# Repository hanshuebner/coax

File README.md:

# coax

Tools for connecting to real [IBM 3270](https://en.wikipedia.org/wiki/IBM_3270) type terminals.

## Documentation

* [protocol](protocol/protocol.md) - Protocol documentation

## Hardware

* [interface1](interface1) - Legacy interface using obsolete National Semiconductor DP8340 and DP8341
* [interface2](interface2) - Modern interface using a Lattice iCE40 FPGA and STM32 microcontroller
* [interface3](interface3) - WiFi interface based on Raspberry Pi Pico W

## Software

* [pycoax](pycoax) - Python interface library

## See Also

* [oec](https://github.com/hanshuebner/oec) - IBM 3270 terminal controller (a replacement for the IBM 3174)

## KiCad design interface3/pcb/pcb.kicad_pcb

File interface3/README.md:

# Interface3 - Raspberry Pi Pico W based 3270 Terminal Adapter

Interface3 is an alternative hardware solution to connect a 3270 coax
terminal to host systems through the oec terminal controller software
written by Andrew Kay.  It consists of a Raspberry Pi Pico-based
hardware interface and MicroPython software that implements the coax
protocol used by 3270 terminals in CUT mode.

## Overview

Interface3 enables communication with IBM 3270 terminals by:

1. **Hardware Interface**: A custom PCB with a Raspberry Pi Pico and
   up to four serial coax interfaces that implement the physical layer
   connection to 3270 terminals.
2. **Protocol Implementation**: The Manchester-encoded coax protocol
   is implemented using PIO blocks of the RP2040 microcontroller.
3. **Connection Modes**: Two connection modes are supported:
   - **Serial Mode**: Direct USB serial connection to a host running
     oec/pycoax, compatible with interface2.  Requires Andrew Kay's
     original [oec](https://github.com/lowobservable/oec).
   - **WiFi Mode**: TCP client that connects to an oec server over
     WiFi using a custom binary protocol.  Requires the modified
     [oec-tcp](https://github.com/hanshuebner/oec-tcp).

## How It Works

### Hardware Layer
The interface uses a Raspberry Pi Pico with custom PCB that provides:
- Two Coax interfaces with proper signal conditioning
- Two additional serial interfaces with TTL levels on a pin header
- LED indicators to display the operating state of the interface
- Momentary button that resets the Raspberry Pi Pico
- USB B socket for power supply and serial connection

### Software Layer

The interface3 software implements the line level Manchester-encoded
protocol in a
[PIO](https://www.raspberrypi.com/news/what-is-pio/) block.  This
offloads the handling of the real-time protocol requirements from the
main ARM CPU and allows the rest of the interface software to be
implemented in MicroPython.  Data between MicroPython and the PIO
blocks is exchanged through DMA, allowing the MicroPython part to
operate only on full frames.

## Installation

### Prerequisites

1. **MicroPython with DMA Extensions**: You need a MicroPython release
   1.26.0 or later to get support for the DMA transfer library
   required by the firmware.

2. **Hardware**: The interface3 PCB with Raspberry Pi Pico installed

3. **Development Tools**:
   - `mpremote` for communicating with the Pico
   - `jq` for JSON processing (used by config-wifi.sh, WiFi mode only)

### Common Installation Steps

1. **Flash MicroPython Firmware**:

   A prebuilt MicroPython image for the Raspberry Pi Pico W (RP2040
   version) can be downloaded from
   [my web site](https://vaxbusters.org/micropython-v1.26.0-rpi-pico-w.uf2).
   Connect the Raspberry Pi Pico W to your workstation using its Micro USB
   port while holding the small white "BOOTSEL" button, then copy the
   image to the USB drive that automatically appears (mounted as
   `/Volumes/RPI-RP2/` on Macs).

2. **Install mpremote**

   You can either install mpremote from your system's package repository
   or using pip.  When using pip, using a virtual environment is
   recommended:

   ```bash
   python -m venv .venv
   . .venv/bin/activate
   pip install mpremote
   ```

3. **Upload and install the firmware** using the install script:

   ```bash
   ./install.sh serial   # For serial mode
   ./install.sh wifi     # For WiFi mode
   ```

   The install script will upload all required files and configure
   the device for the selected mode.

### Updating the Firmware

The firmware restarts the Pico into its USB bootloader when any of its
serial ports is opened at 1200 baud, so a new image can be loaded from
the host it is attached to.  `tools/flash-interface <image.uf2>` does
this end to end: it triggers the restart, waits for the bootloader's
USB drive, copies the image onto it and waits for the interface to come
back.  A board whose firmware predates that hook is put into the
bootloader by hand once, by holding BOOTSEL while pressing reset; the
script waits for it.

### Serial Mode Setup

After running `./install.sh serial`, the device is ready to use.
Connect to the interface using oec (see Usage section below).

### WiFi Mode Setup

After running `./install.sh wifi`, configure WiFi credentials:

```bash
./config-wifi.sh
```

This interactive script will:
- Prompt for WiFi network name and password
- Prompt for the hostname of the oec server
- Create a `config.json` file on the device
- Reset the device to apply the configuration

For testing, you can use my oec server running at netzhansa.com.
It is located in Germany, however, so the latency may be quite
high.  If you run oec on a port other than 3174, you can enter it
after the hostname, colon separated (host:port).

The device stores configuration in a `config.json` file:
```json
{
  "wifi": {
    "ssid": "your_network_name",
    "password": "your_network_password"
  },
  "connect_to": "your-oec-server.example.com"
}
```

## Usage

### Serial Mode

Serial mode requires Andrew Kay's original oec repository:
https://github.com/lowobservable/oec

Run oec with the serial port:

```bash
python -m oec /dev/tty.usbmodem* tn3270 your-host.example.com:23
```

Replace `/dev/tty.usbmodem*` with the actual device path (e.g.,
`/dev/tty.usbmodem1124101` on macOS, `/dev/ttyACM0` on Linux, or
`COM3` on Windows).

The interface presents five serial ports: one per coax port, followed
by the capture port.  Name the port you want explicitly rather than
relying on a glob.

#### Accessing the Python REPL

During startup, the firmware provides a 5-second window to access the
MicroPython REPL for debugging or configuration.  To access the REPL:

1. **Connect to the USB serial port** before or immediately after
   resetting the device.  Use a terminal program or mpremote:
   ```bash
   mpremote connect /dev/tty.usbmodem* repl
   ```

2. **Watch for the startup blink pattern** - the STS LED blinks slowly
   (250ms on, 250ms off) during this 5-second window.

3. **Press Ctrl-C** during this window to interrupt startup and enter
   the REPL.

**Important**: You must connect to the serial port *before* the
startup window expires.  Once the firmware enters protocol mode, the
serial port is used exclusively for SLIP-encoded communication and
keyboard interrupt is disabled.

### WiFi Mode

WiFi mode requires a modified version of oec that acts as a TCP server:
https://github.com/hanshuebner/oec-tcp

Start the oec-tcp server:

```bash
python -m oec --server :3174 tn3270 your-host.example.com:23
```

This starts oec listening on port 3174 for incoming connections from
interface3 devices.  When the interface connects to WiFi successfully,
it will automatically connect to the configured server.

See the [TCP Protocol documentation](./TCP_PROTOCOL.md) for details on
the network protocol.

### Capturing Coax Traffic

The interface can record the coax traffic it exchanges with attached
terminals and hand it to Wireshark.  Capture happens in the firmware,
so both directions of every transaction are recorded as they appear on
the wire, with microsecond timestamps.

Records leave the device on a fifth USB serial port named `Coax
Capture`, which the four command ports are unaffected by.  Write a
capture file with:

```bash
tools/coax-capture --write coax.pcapng
```

To capture from the Wireshark GUI, install the capture plugin and the
dissector once:

```bash
tools/install-wireshark.sh
```

Idle polls are left out unless `--idle-polls` is given, since a
terminal is polled continuously.  See the [capture
documentation](./CAPTURE.md) for the record format, the filtering
options and the pcapng layout.

The interface can also record a link between some other controller and
a terminal, either sitting in the middle of it and forwarding between
two ports, or listening on one:

```bash
tools/coax-capture --forward 0,1 --write link.pcapng
tools/coax-capture --tap 0 --write tap.pcapng
```

See [Passive Capture](./PASSIVE-CAPTURE.md) for how to connect the
interface to a link and what to expect.  Forwarding needs a second coax
port that can transmit; boards built from the earlier layout need the
rework described in [PCB Rework](./PCB-REWORK.md).

## LED Indicators

The interface provides several LED indicators:
- **NET**: Network activity (WiFi mode only)
- **STS**: Status indicator
- **ERR**: Error indicator
- **TX1-4/RX1-4**: Individual channel transmit/receive indicators
- **PICO**: Raspberry Pi Pico onboard LED

### Serial Mode LED Patterns

| LED | Pattern | Description |
|-----|---------|-------------|
| STS | Slow blink (250ms on/off) | **Startup window** - Press Ctrl-C to access REPL |
| STS | Fast blink (100ms on, 200ms off) | **Waiting for connection** - Ready for host to connect |
| STS | Once per second (100ms on, 900ms off) | **Connected** - Normal operation |
| ERR | Continuous fast blink (250ms on/off) | **Fatal error** - Unhandled exception occurred |

### WiFi Mode LED Patterns

| LED | Pattern | Description |
|-----|---------|-------------|
| NET | Fast blink (8Hz) | **Connecting to WiFi** - Attempting to join network |
| NET | Brief on, then off | **WiFi connected** - Successfully joined network |
| NET | On during activity | **Network activity** - Processing commands from server |
| STS | Solid on | **Connecting to server** - Attempting TCP connection |
| STS | Blink (1s on, 1s off) | **Reconnecting** - Connection lost, retrying |
| ERR | Solid on | **WiFi failed** - Could not connect to WiFi network |
| ERR | Solid on | **Coax timeout** - Terminal not responding (clears on success) |

## Quick Reference

| Mode | oec Repository | Command |
|------|----------------|---------|
| Serial | [lowobservable/oec](https://github.com/lowobservable/oec) | `python -m oec /dev/ttyUSB0 tn3270 host:port` |
| WiFi | [hanshuebner/oec-tcp](https://github.com/hanshuebner/oec-tcp) | `python -m oec --server :3174 tn3270 host:port` |

## License

Copyright (c) 2025, Hans Hübner

Permission to use, copy, modify, and/or distribute this software for any
purpose with or without fee is hereby granted, provided that the above
copyright notice and this permission notice appear in all copies.

THE SOFTWARE IS PROVIDED "AS IS" AND THE AUTHOR DISCLAIMS ALL WARRANTIES
WITH REGARD TO THIS SOFTWARE INCLUDING ALL IMPLIED WARRANTIES OF
MERCHANTABILITY AND FITNESS. IN NO EVENT SHALL THE AUTHOR BE LIABLE FOR
ANY SPECIAL, DIRECT, INDIRECT, OR CONSEQUENTIAL DAMAGES OR ANY DAMAGES
WHATSOEVER RESULTING FROM LOSS OF USE, DATA OR PROFITS, WHETHER IN AN
ACTION OF CONTRACT, NEGLIGENCE OR OTHER TORTIOUS ACTION, ARISING OUT OF
OR IN CONNECTION WITH THE USE OR PERFORMANCE OF THIS SOFTWARE.

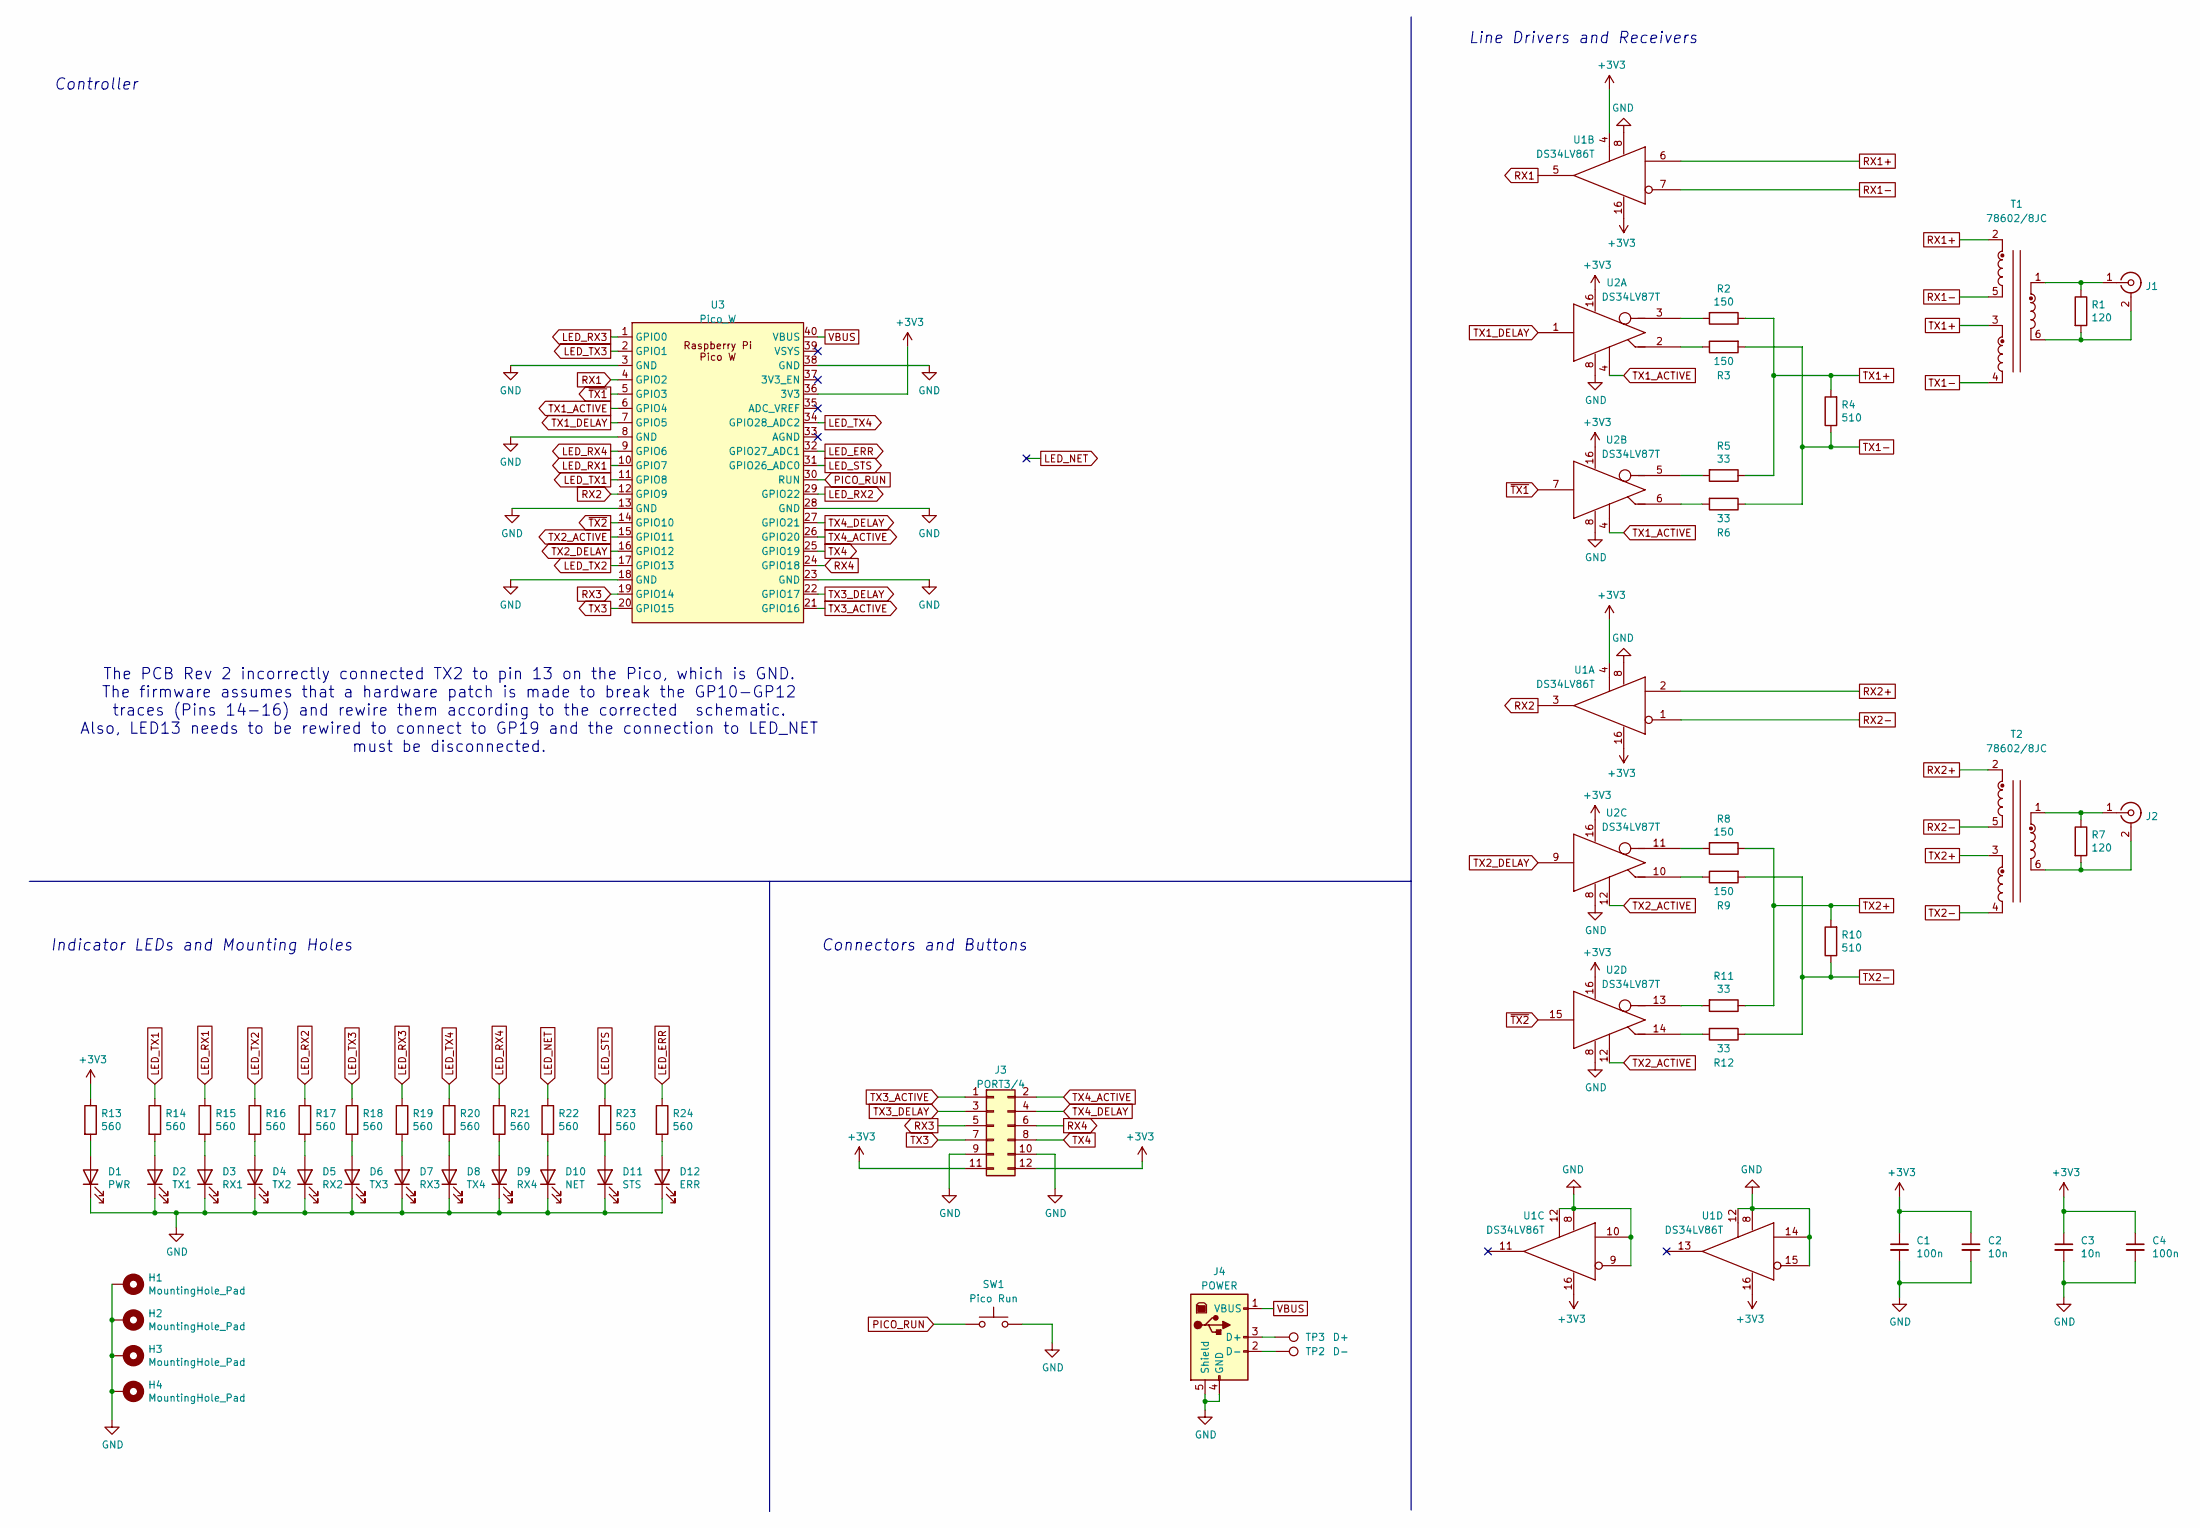
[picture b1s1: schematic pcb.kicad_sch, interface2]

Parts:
C1: 100n; C_0603_1608Metric_Pad1.08x0.95mm_HandSolder; Part EMK107B7104KA-T
C2: 10n; C_0603_1608Metric_Pad1.08x0.95mm_HandSolder; Part HMK107B7103KA-T
C3: 10n; C_0603_1608Metric_Pad1.08x0.95mm_HandSolder; Part EMK107B7104KA-T
C4: 100n; C_0603_1608Metric_Pad1.08x0.95mm_HandSolder; Part HMK107B7103KA-T
D1: PWR; LED_0603_1608Metric; Part 150060VS55040
D2: TX1; LED_0603_1608Metric; Part 150060YS55040
D3: RX1; LED_0603_1608Metric; Part 150060YS55040
D4: TX2; LED_0603_1608Metric; Part 150060YS55040
D5: RX2; LED_0603_1608Metric; Part 150060YS55040
D6: TX3; LED_0603_1608Metric; Part 150060YS55040
D7: RX3; LED_0603_1608Metric; Part 150060YS55040
D8: TX4; LED_0603_1608Metric; Part 150060YS55040
D9: RX4; LED_0603_1608Metric; Part 150060YS55040
D10: NET; LED_0603_1608Metric; Part 150060RS55040
D11: STS; LED_0603_1608Metric; Part 150060RS55040
D12: ERR; LED_0603_1608Metric; Part 150060RS55040
H1, H2, H3, H4: MountingHole_Pad; MountingHole_2.7mm_M2.5_ISO7380_Pad
J1: PORT1; BNC_Amphenol_B6252HB-NPP3G-50_Horizontal; Part 1-1337543-0
J2: PORT2; BNC_Amphenol_B6252HB-NPP3G-50_Horizontal; Part 1-1337543-0
J3: PORT3/4; PinHeader_2x06_P2.54mm_Vertical
J4: POWER; USB_B_OST_USB-B1HSxx_Horizontal
R1, R7: 120; R_0603_1608Metric_Pad0.98x0.95mm_HandSolder; Part RCS0603120RFKEA
R2, R3, R8, R9: 150; R_0603_1608Metric_Pad0.98x0.95mm_HandSolder; Part RCS0603150RFKEA
R4, R10: 510; R_0603_1608Metric_Pad0.98x0.95mm_HandSolder; Part RCS0603510RFKEA
R5, R6, R11, R12: 33; R_0603_1608Metric_Pad0.98x0.95mm_HandSolder; Part RCS060333R0FKEA
R13, R14, R15, R16, R17, R18, R19, R20, R21, R22, R23, R24: 560; R_0603_1608Metric_Pad0.98x0.95mm_HandSolder; Part RCS0603560RFKEA
SW1: Pico Run; SW_Push_1P1T_NO_6x6mm_H9.5mm
T1, T2: 78602/8JC; Murata_786J; Part 78602/8JC
TP2: D-; TestPoint_Pad_D2.0mm
TP3: D+; TestPoint_Pad_D2.0mm
U1: DS34LV86T; SOIC-16_3.9x9.9mm_P1.27mm; Part DS34LV86T
U2: DS34LV87T; SOIC-16_3.9x9.9mm_P1.27mm; Part DS34LV87T
U3: Pico_W; RPi_Pico_W_SMD_TH

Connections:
+3V3: C1.1, C2.1, C3.1, C4.1, J3.11, J3.12, R13.1, U1.4 (ENABLE), U1.16 (VCC), U2.16 (VCC), U3.36 (3V3)
GND: C1.2, C2.2, C3.2, C4.2, D1.1 (K), D2.1 (K), D3.1 (K), D4.1 (K), D5.1 (K), D6.1 (K), D7.1 (K), D8.1 (K), D9.1 (K), D10.1 (K), D11.1 (K), D12.1 (K), H1.1 (1_1), H2.1 (1_1), H3.1 (1_1), H4.1 (1_1), J3.9, J3.10, J4.4 (GND), J4.5 (Shield), SW1.2, U1.8 (GND), U1.9 (E-), U1.10 (E+), U1.12 (ENABLE), U1.14 (E+), U1.15 (E-), U2.8 (GND), U3.3 (GND), U3.8 (GND), U3.13 (GND), U3.18 (GND), U3.23 (GND), U3.28 (GND), U3.38 (GND)
LED_ERR: R24.1, U3.32 (GPIO27_ADC1)
LED_NET: R22.1
LED_RX1: R15.1, U3.10 (GPIO7)
LED_RX2: R17.1, U3.29 (GPIO22)
LED_RX3: R19.1, U3.1 (GPIO0)
LED_RX4: R21.1, U3.9 (GPIO6)
LED_STS: R23.1, U3.31 (GPIO26_ADC0)
LED_TX1: R14.1, U3.11 (GPIO8)
LED_TX2: R16.1, U3.17 (GPIO13)
LED_TX3: R18.1, U3.2 (GPIO1)
LED_TX4: R20.1, U3.34 (GPIO28_ADC2)
unnamed: D1.2 (A), R13.2
unnamed: D2.2 (A), R14.2
unnamed: D3.2 (A), R15.2
unnamed: D4.2 (A), R16.2
unnamed: D5.2 (A), R17.2
unnamed: D6.2 (A), R18.2
unnamed: D7.2 (A), R19.2
unnamed: D8.2 (A), R20.2
unnamed: D9.2 (A), R21.2
unnamed: D10.2 (A), R22.2
unnamed: D11.2 (A), R23.2
unnamed: D12.2 (A), R24.2
unnamed: J1.2 (Ext), R1.2, T1.6
unnamed: J1.1 (In), R1.1, T1.1
unnamed: J2.2 (Ext), R7.2, T2.6
unnamed: J2.1 (In), R7.1, T2.1
unnamed: J4.3 (D+), TP3.1 (1_1)
unnamed: J4.2 (D-), TP2.1 (1_1)
unnamed: R3.1, U2.2 (OUT+)
unnamed: R2.2, U2.3 (OUT-)
unnamed: R6.2, U2.6 (OUT+)
unnamed: R5.2, U2.5 (OUT-)
unnamed: R9.1, U2.10 (OUT+)
unnamed: R8.2, U2.11 (OUT-)
unnamed: R12.2, U2.14 (OUT+)
unnamed: R11.2, U2.13 (OUT-)
PICO_RUN: SW1.1, U3.30 (RUN)
RX1: U1.5 (OUT), U3.4 (GPIO2)
RX1+: T1.2, U1.6 (E+)
RX1-: T1.5, U1.7 (E-)
RX2: U1.3 (OUT), U3.12 (GPIO9)
RX2+: T2.2, U1.2 (E+)
RX2-: T2.5, U1.1 (E-)
RX3: J3.5, U3.19 (GPIO14)
RX4: J3.6, U3.24 (GPIO18)
TX1+: R2.1, R4.2, R5.1, T1.3
TX1-: R3.2, R4.1, R6.1, T1.4
TX1_ACTIVE: U2.4 (ENABLE), U3.6 (GPIO4)
TX1_DELAY: U2.1 (INPUT), U3.7 (GPIO5)
TX2+: R8.1, R10.2, R11.1, T2.3
TX2-: R9.2, R10.1, R12.1, T2.4
TX2_ACTIVE: U2.12 (ENABLE), U3.15 (GPIO11)
TX2_DELAY: U2.9 (INPUT), U3.16 (GPIO12)
TX3: J3.7, U3.20 (GPIO15)
TX3_ACTIVE: J3.1, U3.21 (GPIO16)
TX3_DELAY: J3.3, U3.22 (GPIO17)
TX4: J3.8, U3.25 (GPIO19)
TX4_ACTIVE: J3.2, U3.26 (GPIO20)
TX4_DELAY: J3.4, U3.27 (GPIO21)
VBUS: J4.1 (VBUS), U3.40 (VBUS)
~TX1: U2.7 (INPUT), U3.5 (GPIO3)
~TX2: U2.15 (INPUT), U3.14 (GPIO10)

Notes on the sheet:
Connectors and Buttons
Line Drivers and Receivers
Controller
The PCB Rev 2 incorrectly connected TX2 to pin 13 on the Pico, which is GND. The firmware assumes that a hardware patch is made to break the GP10-GP12 traces (Pins 14-16) and rewire them according to the corrected schematic. Also, LED13 needs to be rewired to connect to GP19 and the connection to L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
Indicator LEDs and Mounting Holes

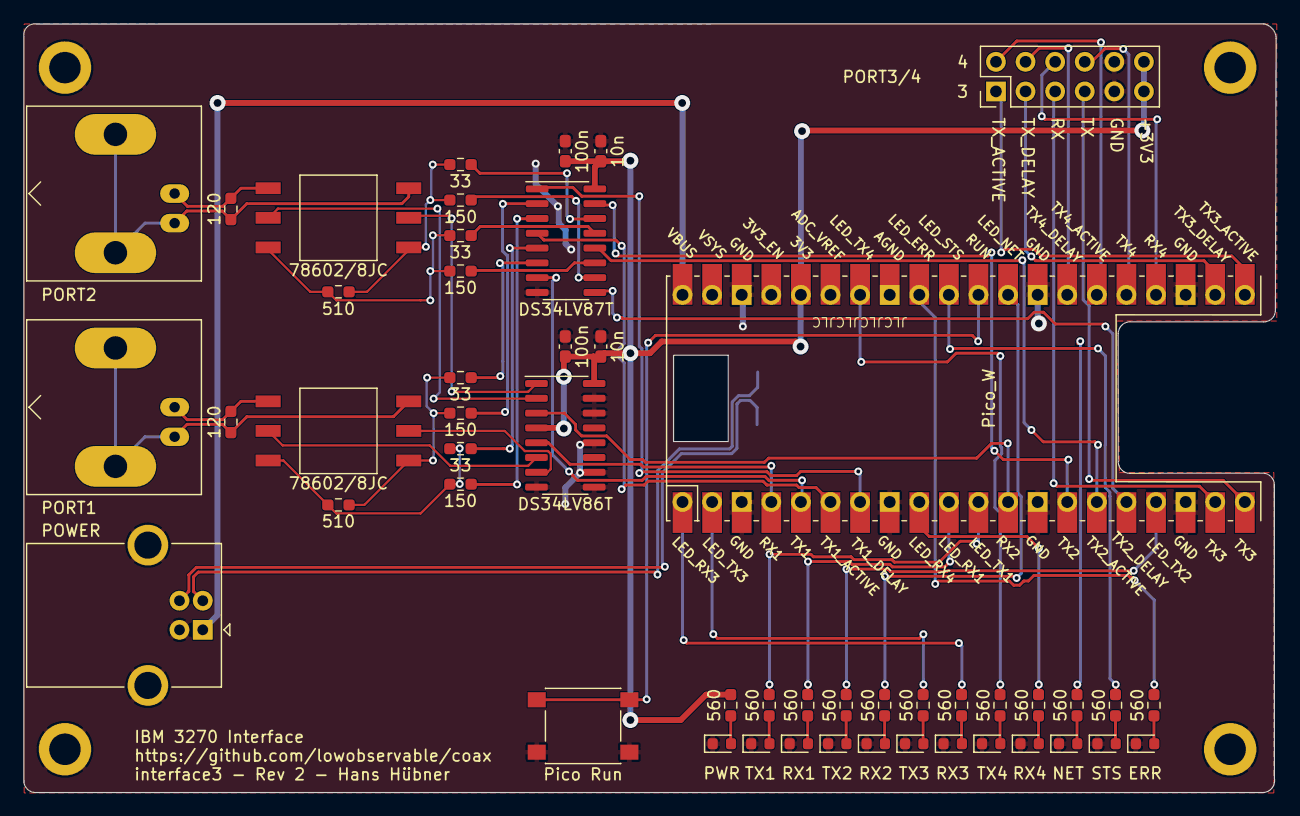
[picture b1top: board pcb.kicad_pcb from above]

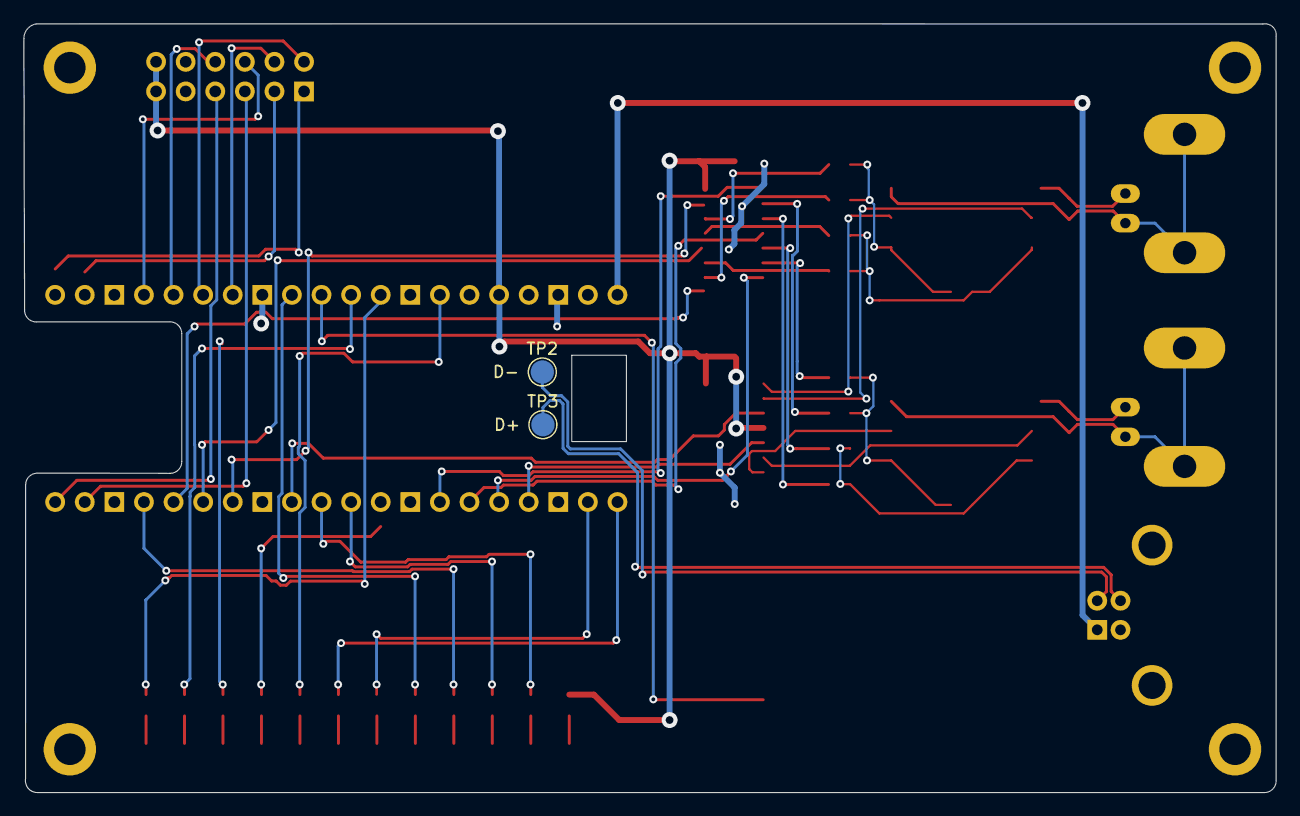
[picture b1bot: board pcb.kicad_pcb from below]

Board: 2 copper layers, 107.5 x 66.0 mm, 56 parts (2 on the bottom side), 64 nets.

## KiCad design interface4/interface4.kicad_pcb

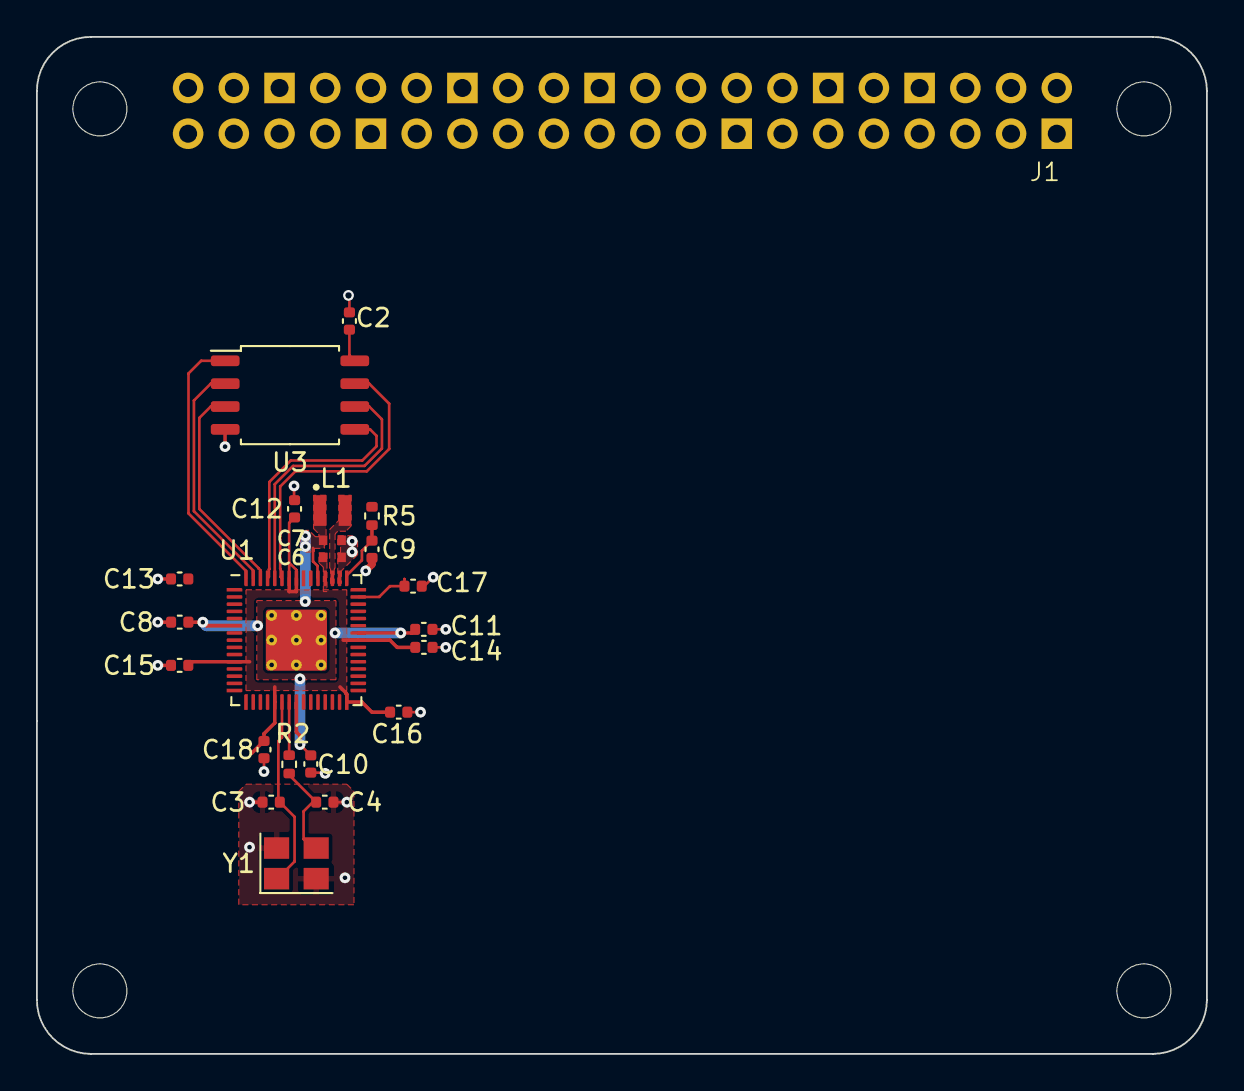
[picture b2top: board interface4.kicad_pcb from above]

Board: 2 copper layers, 65.0 x 56.5 mm, 23 parts (0 on the bottom side), 14 nets.

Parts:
C2, C8, C11, C12, C13, C14, C15, C16, C17, C18: 100n; C_0402_1005Metric
C3, C4: 15p; C_0402_1005Metric
C6, C7: 4.7u; C_0402_1005Metric_small_pads
C9, C10: 4.7u; C_0402_1005Metric
J1: RPi_GPIO; RPI_Hat_B+
L1: 3.3u; L_pol_2016
R2: 1k; R_0402_1005Metric
R5: 33; R_0402_1005Metric
U1: RP2350_60QFN; RP2350-QFN-60-1EP_7x7_P0.4mm_EP3.4x3.4mm_ThermalVias
U3: W25Q128JVS; SOIC-8_5.23x5.23mm_P1.27mm
Y1: ABM8-272-T3; Crystal_SMD_3225-4Pin_3.2x2.5mm

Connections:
+1V1: C7.1, C8.1, C10.1, C11.1, L1.1, U1.6 (DVDD), U1.23 (DVDD), U1.39 (DVDD), U1.50 (VREG_FB)
+3V3: C2.1, C6.1, C12.1, C13.1, C14.1, C15.1, C16.1, C17.1, C18.1, R5.1, U1.1 (IOVDD), U1.11 (IOVDD), U1.20 (IOVDD), U1.30 (IOVDD), U1.38 (IOVDD), U1.44 (ADC_AVDD), U1.45 (IOVDD), U1.49 (VREG_VIN), U1.53 (USB_OTP_VDD), U1.54 (QSPI_IOVDD), U3.8 (VCC)
/QSPI_SCLK: U1.56 (QSPI_SCLK), U3.6 (CLK)
/QSPI_SD0: U1.57 (QSPI_SD0), U3.5 (DI(IO0))
/QSPI_SD1: U1.59 (QSPI_SD1), U3.2 (DO(IO1))
/QSPI_SD2: U1.58 (QSPI_SD2), U3.3 (IO2)
/QSPI_SD3: U1.55 (QSPI_SD3), U3.7 (IO3)
/QSPI_SS: U1.60 (QSPI_SS), U3.1 (~CS)
/VREG_AVDD: C9.1, R5.2, U1.46 (VREG_AVDD)
/VREG_LX: L1.2, U1.48 (VREG_LX)
/XIN: C3.1, U1.21 (XIN), Y1.1
/XOUT: R2.1, U1.22 (XOUT)
GND: C2.2, C3.2, C4.2, C6.2, C7.2, C8.2, C9.2, C10.2, C11.2, C12.2, C13.2, C14.2, C15.2, C16.2, C17.2, C18.2, U1.47 (VREG_PGND), U1.61 (GND), U3.4 (GND), Y1.2, Y1.4
unnamed: C4.1, R2.2, Y1.3

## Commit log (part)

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2023-08-01 refactor serial interface transmit recieve message
2023-08-04 add beginnings of interface3 (rp2040 based)
    Can send a test word and receive it
2023-08-04 update pycoax workflow for new action versions
2023-08-04 (re)organize and remove js stuff
2023-08-04 use kwargs for clarity
2023-08-04 begin interface3 pcb design
2023-08-04 improve interface3 schematic, unify pin names
2023-08-04 generate TX_ACTIVE signal
2023-08-05 add pattern generator for pulsegen
2023-08-07 some pcb work
2023-08-07 fix frame start detection, half-duplex now
2023-08-12 led work
2023-08-12 pcb work
2023-08-12 add NS chipset data sheets
2023-08-14 fix frame formatting, now matches interface1 closely
2023-08-14 interface3 timeout handling in pycoax improved
2023-08-14 fix tests
2023-09-03 checkpoint work
2023-09-03 fix receiver synchronization
2023-09-07 interface3 pcb work
2023-09-08 interface3 version 1 pcb sent to jlcpcb
2023-09-10 restart pios in each transaction
2023-09-10 remove interface1 test sender
2023-09-14 add leds module
2023-09-16 fix PCB issues found in v1
    closes #1, #2, #3
2023-09-16 improve blinkenlights
2025-08-15 finish layout (again) - this version has not been produced yet
2025-08-15 update upload-artifact action to v4
2025-08-15 v2 sent to jlcpcb (with usb wiring)
2025-08-17 remove code to read wifi config from macos
2025-08-17 TCP protocol
2025-08-19 update workflows
2025-08-23 Adapt to official MicroPython rp2.DMA API
2025-08-23 dependencies
2025-08-23 readme update
2025-08-23 point to temporary for in docs for now
2025-08-23 fix markdown syntax error
2025-08-23 More README tweaks
2025-08-23 README formatting fixes
2025-08-23 fix requests version
2025-08-23 remove rp_devices.py as it is no longer needed
2025-08-26 Clarify WiFi configuration in README
2025-08-31 convert to asyncio
2025-08-31 detached polling
2025-08-31 set TCP_NODELAY
2025-08-31 Lower delay
2025-08-31 suppress PollAck for tcp interface
2025-08-31 fix syntax error
2025-08-31 switch interface3 to make outbound connections
2025-09-01 reversed client/server role on tcp interface
2025-09-01 handle interface disconnect/reconnect
2025-09-05 protect access to connected by lock
2025-09-05 threaded server
2025-09-05 remove polls from tcp connection
2025-09-05 Improved config-wifi UX
2025-09-05 remove locks
2025-09-06 remove listen/accept logic from interface
2025-09-06 logging
2025-09-07 remove extra timing report
2025-09-07 refactor
2025-09-07 update docs
2025-09-21 recover from lost polls
2025-10-18 don't need leds in main
2025-10-18 add beginnings of serial protocol implementation
2025-10-20 beginnings of (USB) serial protocol implementation
2026-01-25 working on interface3 serial mode
2026-01-25 Make serial mode interface2 compatible
2026-01-25 installation routine
2026-01-25 undo fifo flushing, increase minimum timeout for transact
2026-01-27 add interface confidence test
2026-01-28 add keyboard polling to confidence test
2026-04-07 Save interface4 work
